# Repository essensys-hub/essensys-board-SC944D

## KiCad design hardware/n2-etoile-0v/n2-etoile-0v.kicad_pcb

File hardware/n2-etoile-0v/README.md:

# N2 « étoile 0 V » – carte passive sur rail DIN

Change OpenSpec : `i2c-surge-protection-2026-10-007`, tâche 4.1 (ticket essensys-hub/essensys-board-SC944D#1).
Références : `design.md` section D4 (N2), `specs/aux-box-interconnect/spec.md`.

## Fonction

N2 remplace le chaînage BP → BA1 → BA2 → BA3 par une **étoile** : le bus du BP (J31) arrive sur la carte
et repart vers chaque BA par un port dédié. Le 0 V de chaque BA rejoint celui du BP par un **plan 0 V double face**,
avec deux faisceaux AWG20 par BA (J1 et J2 du BA). Le 0 V du BP est doublé par une queue de cochon AWG20
soudée sur la broche traversante J31-3. But : relever le seuil de courant d'équilibrage à partir duquel
les écrêteurs I2C conduisent (au moins 4 fois la référence, à mesurer en 4.3), et garder l'écart statique de 0 V
sous 0,05 V.

Par port BA :

- **cavalier JPn** (embase 2×3 au pas de 2,54 mm, 3 shunts) qui coupe SDA, SCL et +15 V ; le 0 V n'est jamais coupé.
  Un pont 2×3 (boîtier femelle 2×3 avec 3 boucles) permet d'ouvrir les trois lignes en une seule manœuvre ;
- **PTC Fn** (CMS 1812, 30 V au moins) sur le +15 V, **puis TVS Dn SMAJ16A** entre le +15 V du port et le 0 V.
  Une TVS en court-circuit ne fait déclencher que la PTC de son port : les autres BA restent alimentés.

Aucun composant actif, aucun firmware, aucune retouche des BA.

## Brochage (WR-MPC3 2×2, compatible Würth 66200421122)

| Broche | Signal |
|---|---|
| 1 | SDA |
| 2 | SCL |
| 3 | 0 V |
| 4 | +15 V |

| Repère | Rôle |
|---|---|
| J1 | Entrée BP, vers J31 du BP |
| J8 | Pastille (Ø 1,25 mm) pour la queue de cochon AWG20 vers J31-3 du BP |
| J2 / J3 | BA1 SC940D, vers J1 / J2 du BA |
| J4 / J5 | BA2 SC941C, vers J1 / J2 du BA |
| J6 / J7 | BA3 SC942C, vers J1 / J2 du BA |
| JP1 / JP2 / JP3 | Cavalier du port BA1 / BA2 / BA3 (impairs côté BP, pairs côté port) |
| F1–F3, D1–D3 | PTC puis TVS du +15 V de chaque port |
| H1–H4 | Trous M3 non métallisés, **non reliés** (fixation sur support DIN isolant) |

Nets : `SDA_BP`, `SCL_BP`, `+15V_BP`, `0V` ; par port `SDA_BAn`, `SCL_BAn`, `+15V_SWn` (après cavalier), `+15V_BAn` (après PTC).

## Carte

- 110 × 68 mm, FR-4 1,6 mm, 2 couches, **cuivre 2 oz (70 µm) demandé**, HASL, vernis vert, sérigraphie blanche.
- Plan 0 V sur les deux faces (raccord plein, sans thermique), vias de couture, liaison J31-3 → pastille J8 en piste de 3 mm.
- Pistes : +15 V 1,5 à 2 mm, SDA/SCL 0,5 mm ; tronc en peigne depuis J1, une descente par port.
- Support DIN : à monter sur un porte-carte DIN **isolant** (profilé plastique pour carte de 68 mm, ou entretoises nylon M3 sur adaptateur DIN). Les trous de fixation ne sont reliés à rien.

## Fichiers

| Fichier | Contenu |
|---|---|
| `n2-etoile-0v.kicad_pro/.kicad_sch/.kicad_pcb` | Projet KiCad 9 |
| `export/n2-etoile-0v-schema.pdf` | Schéma |
| `export/n2-etoile-0v-bom.csv` | BOM |
| `export/n2-etoile-0v-gerber.zip` | Gerber, perçages Excellon, plan de perçage, job Gerber |
| `export/n2-etoile-0v-pcb-{top,bottom}.{png,svg}` | Rendus 3D et tracés cuivre |
| `rapports/erc.rpt`, `rapports/drc.rpt` | ERC et DRC (avec parité schéma) : 0 erreur, 0 avertissement |
| `scripts/` | Générateurs (`build.sh` régénère tout avec KiCad 9) |

## BOM

| Repères | Qté | Composant | Note |
|---|---|---|---|
| J1–J7 | 7 | Embase WR-MPC3 2×2 verticale THT, Würth 66200421122 (empreinte Molex Micro-Fit 3.0 43045-0412) | |
| F1–F3 | 3 | PTC CMS 1812, 30 V au moins, ex. Littelfuse 1812L050/30MR | Courant de maintien à fixer (voir limites) |
| D1–D3 | 3 | TVS SMAJ16A (SMA) | |
| JP1–JP3 | 3 | Embase mâle 2×3, pas de 2,54 mm | + 9 shunts, ou 3 ponts 2×3 |
| J8 | – | Pastille, pas de composant | Queue de cochon AWG20 |
| – | 1 | Porte-carte DIN isolant + 4 vis/entretoises M3 nylon | Hors BOM KiCad |

Faisceaux (tâche 4.2) : 7 cordons AWG20 2×2 WR-MPC3 femelle des deux côtés, 15 cm au plus, sertis à l'outil.

## Consignes de pose

- **Le 0 V n'est jamais relié au PE** : pas de borne PE sur la carte ni dans le coffret domotique, support DIN isolant,
  aucune vis de fixation reliée au 0 V.
- Faisceaux AWG20 de **15 cm au plus**, isolés, ni vert-jaune ni bleu clair, repérés aux deux extrémités des liaisons 0 V :
  **« 0 V TBTS – NE PAS RELIER À LA TERRE »**.
- La queue de cochon vers J31-3 est soudée sur la broche traversante pendant la dépose du BP, jamais sur une pastille CMS,
  avec un arrêt de traction ; elle est repérée comme les autres liaisons 0 V.
- Câbler **J1 et J2 de chaque BA** (les deux faisceaux comptent dans le seuil). Ne plus chaîner les BA entre eux.
- Déconnecter un BA : ouvrir JPn (SDA, SCL et +15 V coupés, 0 V conservé), sans toucher au câblage 230 V.
- Ne jamais piloter une armoire réelle pendant les essais.

## Vérifications restantes (banc)

- **4.2** faisceaux : moins de 60 mΩ par conducteur, contacts compris ; repérage contrôlé.
- **4.3** seuil d'équilibrage en onde 8/20 et sur un front de 1 Ipk/µs : au moins 4 fois la référence de la chaîne d'origine ;
  écart statique de 0 V entre J31-3 du BP et J1-3 de chaque BA d'au plus 0,05 V à consommation maximale.
- **4.4** sélectivité des PTC : sortie en court-circuit 60 s, autres sorties à 14 V ou plus en 5 s sans déclencher le BP ;
  autres BA de nouveau acquittés moins de 10 s après ouverture du cavalier ; remontée en 120 s au plus ;
  aucun déclenchement en 24 h à 50 °C à consommation maximale.

## Limites

- **Empreintes à vérifier** sur les fiches techniques avant fabrication : la WR-MPC3 66200421122 est placée avec l'empreinte
  Molex Micro-Fit 3.0 43045-0412 (pas de 3 mm, deux plots de centrage Ø 1,02 mm) ; numérotation des broches à contrôler
  face au brochage du BA (1 SDA, 2 SCL, 3 0 V, 4 +15 V) et à l'orientation du détrompeur.
- **PTC** : la référence 1812L050/30MR est indicative. Le courant de maintien à 50 °C doit valoir au moins 1,5 fois le
  courant de BA_ALIM d'un BA relais collés (design D3) ; à mesurer, puis à valider en 4.4. Si aucune PTC 1812 ne convient,
  changer l'empreinte (radiale).
- Le cavalier à 3 shunts demande trois gestes ; pour la « manœuvre unique » de la spec, utiliser un pont 2×3.
- Cuivre 2 oz : à préciser à la commande (non porté par l'empilage KiCad, seulement par la sérigraphie de fabrication).
- Pas de TVS de données sur SDA/SCL (non demandée pour N2) ; modèles 3D non vérifiés.

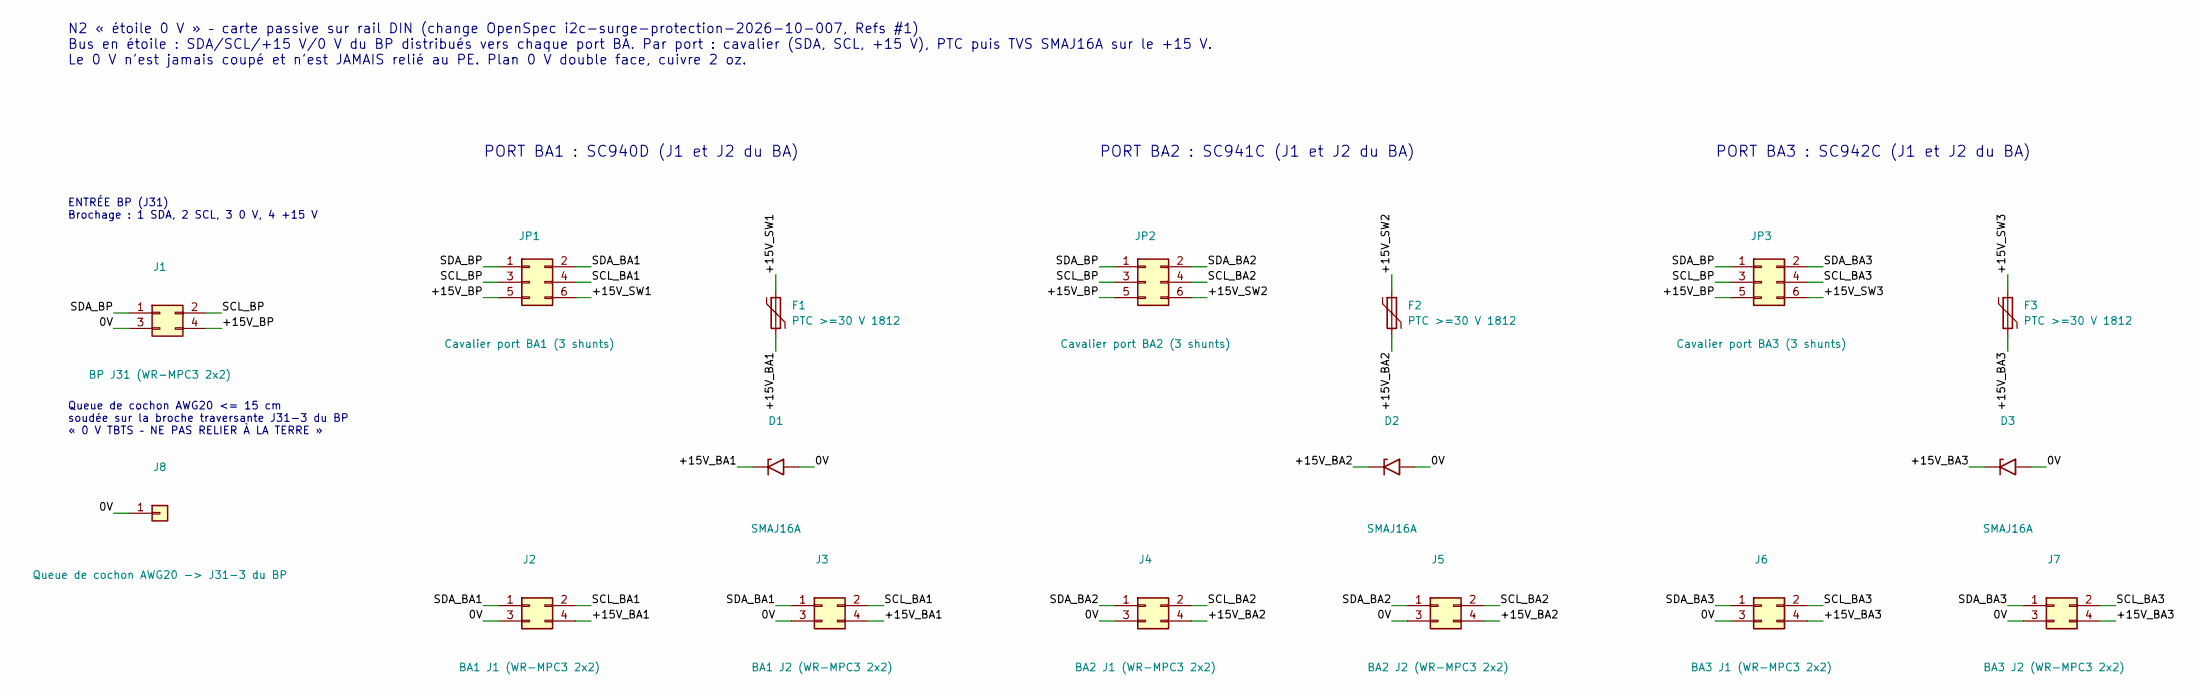
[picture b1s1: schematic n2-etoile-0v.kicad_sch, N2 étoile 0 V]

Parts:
D1, D2, D3: SMAJ16A; D_SMA; MPN SMAJ16A
F1, F2, F3: PTC >=30 V 1812; Fuse_1812_4532Metric; MPN 1812L050/30MR (à confirmer : Ihold@50°C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
J1: BP J31 (WR-MPC3 2x2); Molex_Micro-Fit_3.0_43045-0412_2x02_P3.00mm_Vertical; MPN 66200421122 (WR-MPC3 2x2, vertical, THT)
J2: BA1 J1 (WR-MPC3 2x2); Molex_Micro-Fit_3.0_43045-0412_2x02_P3.00mm_Vertical; MPN 66200421122 (WR-MPC3 2x2, vertical, THT)
J3: BA1 J2 (WR-MPC3 2x2); Molex_Micro-Fit_3.0_43045-0412_2x02_P3.00mm_Vertical; MPN 66200421122 (WR-MPC3 2x2, vertical, THT)
J4: BA2 J1 (WR-MPC3 2x2); Molex_Micro-Fit_3.0_43045-0412_2x02_P3.00mm_Vertical; MPN 66200421122 (WR-MPC3 2x2, vertical, THT)
J5: BA2 J2 (WR-MPC3 2x2); Molex_Micro-Fit_3.0_43045-0412_2x02_P3.00mm_Vertical; MPN 66200421122 (WR-MPC3 2x2, vertical, THT)
J6: BA3 J1 (WR-MPC3 2x2); Molex_Micro-Fit_3.0_43045-0412_2x02_P3.00mm_Vertical; MPN 66200421122 (WR-MPC3 2x2, vertical, THT)
J7: BA3 J2 (WR-MPC3 2x2); Molex_Micro-Fit_3.0_43045-0412_2x02_P3.00mm_Vertical; MPN 66200421122 (WR-MPC3 2x2, vertical, THT)
J8: Queue de cochon AWG20 -> J31-3 du BP; SolderWire-0.75sqmm_1x01_D1.25mm_OD3.5mm
JP1: Cavalier port BA1 (3 shunts); PinHeader_2x03_P2.54mm_Vertical
JP2: Cavalier port BA2 (3 shunts); PinHeader_2x03_P2.54mm_Vertical
JP3: Cavalier port BA3 (3 shunts); PinHeader_2x03_P2.54mm_Vertical

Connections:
/0V: D1.2 (A2), D2.2 (A2), D3.2 (A2), J1.3, J2.3, J3.3, J4.3, J5.3, J6.3, J7.3, J8.1
/+15V_BA1: D1.1 (A1), F1.2, J2.4, J3.4
/+15V_BA2: D2.1 (A1), F2.2, J4.4, J5.4
/+15V_BA3: D3.1 (A1), F3.2, J6.4, J7.4
/+15V_BP: J1.4, JP1.5, JP2.5, JP3.5
/+15V_SW1: F1.1, JP1.6
/+15V_SW2: F2.1, JP2.6
/+15V_SW3: F3.1, JP3.6
/SCL_BA1: J2.2, J3.2, JP1.4
/SCL_BA2: J4.2, J5.2, JP2.4
/SCL_BA3: J6.2, J7.2, JP3.4
/SCL_BP: J1.2, JP1.3, JP2.3, JP3.3
/SDA_BA1: J2.1, J3.1, JP1.2
/SDA_BA2: J4.1, J5.1, JP2.2
/SDA_BA3: J6.1, J7.1, JP3.2
/SDA_BP: J1.1, JP1.1, JP2.1, JP3.1

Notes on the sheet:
ENTRÉE BP (J31) Brochage : 1 SDA, 2 SCL, 3 0 V, 4 +15 V
Queue de cochon AWG20 <= 15 cm soudée sur la broche traversante J31-3 du BP « 0 V TBTS – NE PAS RELIER À LA TERRE »
PORT BA1 : SC940D (J1 et J2 du BA)
PORT BA2 : SC941C (J1 et J2 du BA)
PORT BA3 : SC942C (J1 et J2 du BA)
N2 « étoile 0 V » – carte passive sur rail DIN (change OpenSpec i2c-surge-protection-2026-10-007, Refs #1) Bus en étoile : SDA/SCL/+15 V/0 V du BP distribués vers chaque port BA. Par port : cavalier (SDA, SCL, +15 V), PTC puis TVS SMAJ16A sur le +15 V. Le 0 V n'est jamais coupé et n'est JAMAIS reli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

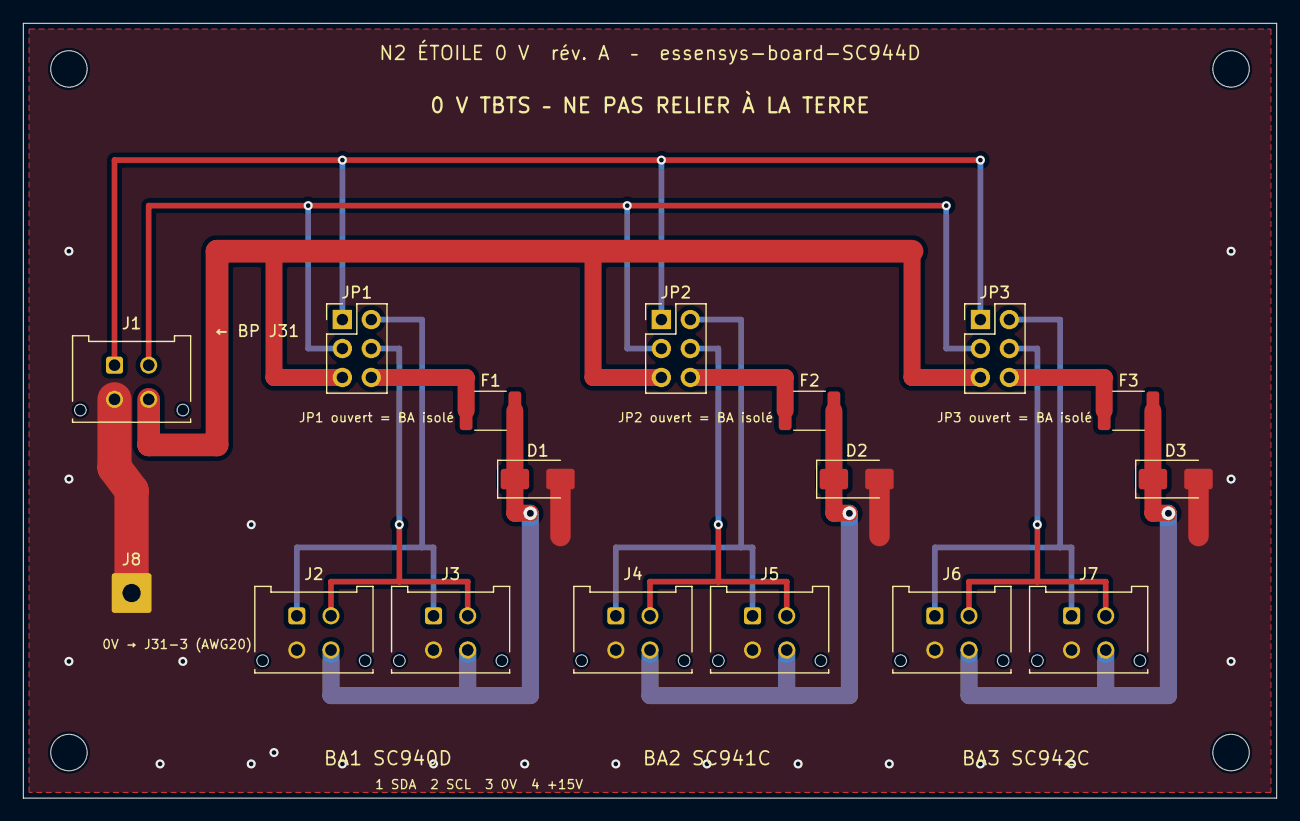
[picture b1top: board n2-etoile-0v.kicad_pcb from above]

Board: 2 copper layers, 110.0 x 68.0 mm, 21 parts (0 on the bottom side), 16 nets.

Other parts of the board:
H1, H2, H3, H4: M3 isolé; MountingHole_3.2mm_M3

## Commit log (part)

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2025-12-26 docs: generate module documentation (SC944D) - exclude large zip
2025-12-26 docs: add detailed firmware algo documentation (SC944D)
2025-12-26 chore: update project configuration and documentation resources
2025-12-26 docs: refine firmware documentation (server interactions, lights, BA protocol) and update index
2025-12-26 chore: enable mermaid diagram support in mkdocs
2025-12-26 docs: add dedicated I2C protocol documentation and update navigation
2025-12-26 docs: add mermaid diagrams and force read analysis to i2c documentation
2025-12-26 Deployed 3c62480 with MkDocs version: 1.6.1
2026-01-10 Add Docker-based Linux build environment
